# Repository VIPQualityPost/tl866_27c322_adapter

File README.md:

# tl866_27c322_adapter
A small footprint adapter that can be used for programming 27C* type EEPROMs on a TL866 II programmer. This programmer is abundantly available and cheap but does not support DIP packages larger than 2x20 pins. This adapter allows you to manually address the upper 3 bits of the memory so you can program these larger chips. Unlike some of the other cheaper adapters online, this one is very small, and uses a rotary bit switch to select the active bank with "true" code, so that you don't have to worry about switching the binary banks in the right order or with inverted output.

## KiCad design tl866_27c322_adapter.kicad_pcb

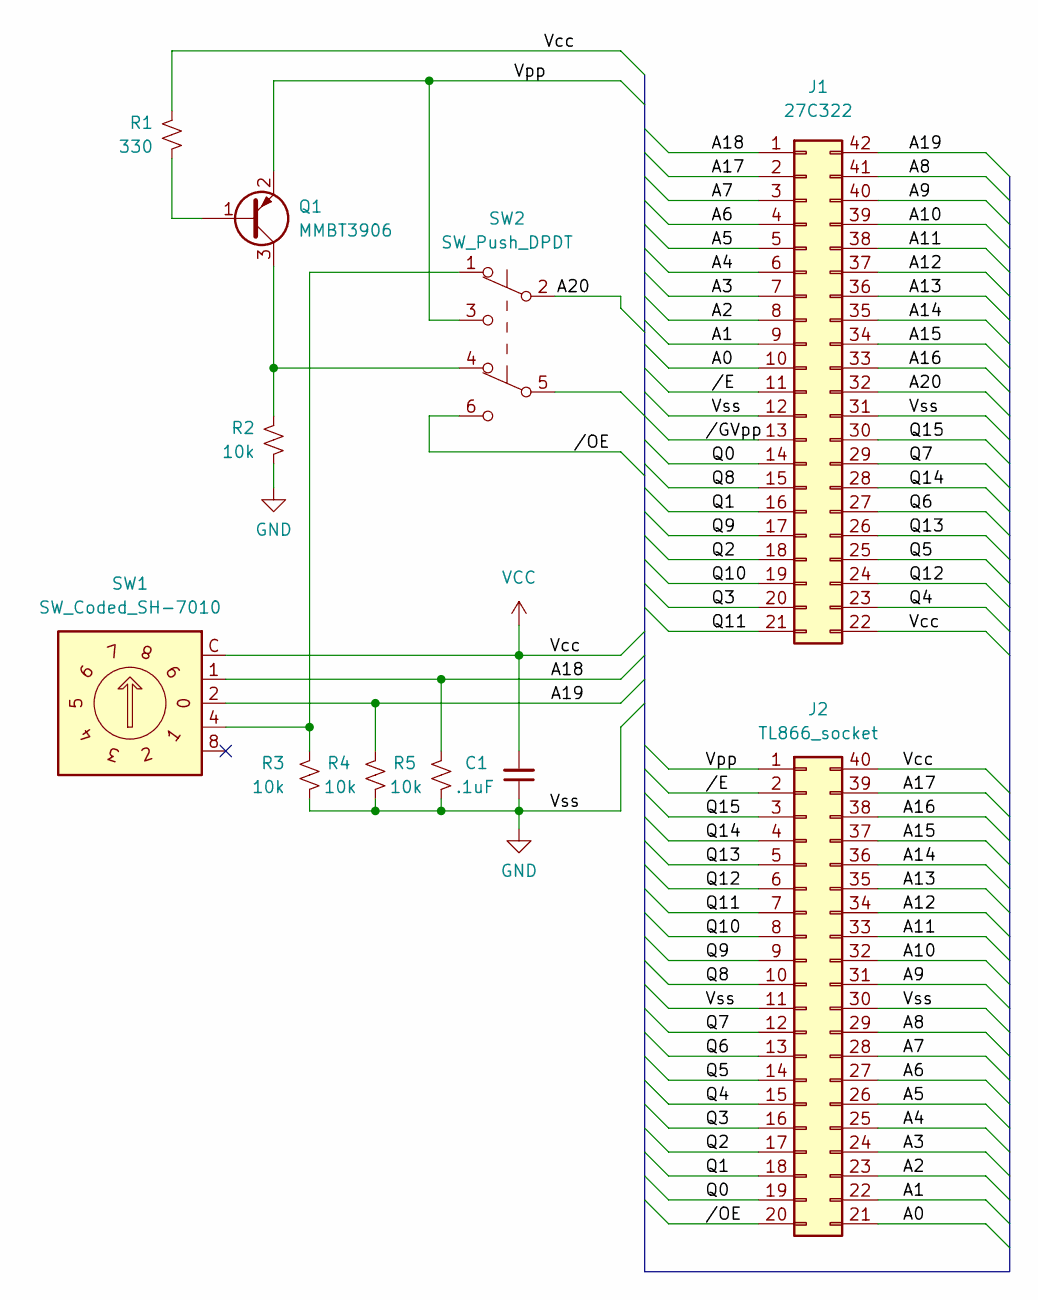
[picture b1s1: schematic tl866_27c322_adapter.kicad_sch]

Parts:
C1: .1uF; R_0805_2012Metric
J1: 27C322; DIP-42_W15.24mm
J2: TL866_socket; DIP-40_W15.24mm
Q1: MMBT3906; SOT-23
R1: 330; R_0805_2012Metric
R2, R3, R4, R5: 10k; R_0805_2012Metric
SW1: SW_Coded_SH-7010; Nidec_Copal_SH-7010B
SW2: SW_Push_DPDT; JS202011JCQN

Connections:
/A0: J1.10, J2.21
/A1: J1.9, J2.22
/A2: J1.8, J2.23
/A3: J1.7, J2.24
/A4: J1.6, J2.25
/A5: J1.5, J2.26
/A6: J1.4, J2.27
/A7: J1.3, J2.28
/A8: J1.41, J2.29
/A9: J1.40, J2.31
/A10: J1.39, J2.32
/A11: J1.38, J2.33
/A12: J1.37, J2.34
/A13: J1.36, J2.35
/A14: J1.35, J2.36
/A15: J1.34, J2.37
/A16: J1.33, J2.38
/A17: J1.2, J2.39
/A18: J1.1, R5.2, SW1.1
/A19: J1.42, R4.2, SW1.2
/A20: J1.32, SW2.2 (B)
/Q0: J1.14, J2.19
/Q1: J1.16, J2.18
/Q2: J1.18, J2.17
/Q3: J1.20, J2.16
/Q4: J1.23, J2.15
/Q5: J1.25, J2.14
/Q6: J1.27, J2.13
/Q7: J1.29, J2.12
/Q8: J1.15, J2.10
/Q9: J1.17, J2.9
/Q10: J1.19, J2.8
/Q11: J1.21, J2.7
/Q12: J1.24, J2.6
/Q13: J1.26, J2.5
/Q14: J1.28, J2.4
/Q15: J1.30, J2.3
/Vpp: J2.1, Q1.2 (E), SW2.3 (C)
//E: J1.11, J2.2
//GVpp: J1.13, SW2.5 (B)
//OE: J2.20, SW2.6 (C)
GND: C1.1, J1.12, J1.31, J2.11, J2.30, R2.1, R3.1, R4.1, R5.1
unnamed: Q1.1 (B), R1.1
unnamed: Q1.3 (C), R2.2, SW2.4 (A)
unnamed: R3.2, SW1.4, SW2.1 (A)
VCC: C1.2, J1.22, J2.40, R1.2, SW1.C

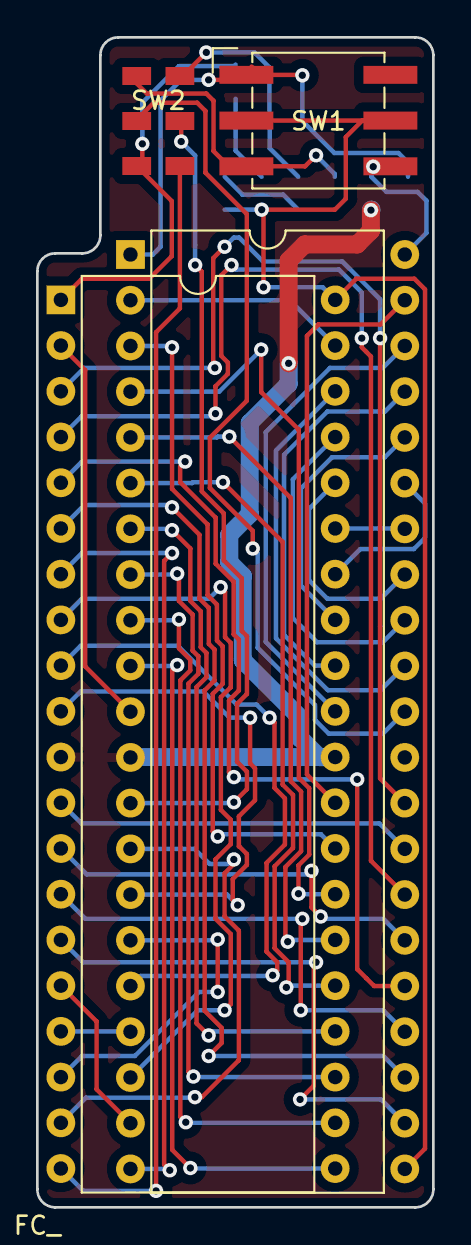
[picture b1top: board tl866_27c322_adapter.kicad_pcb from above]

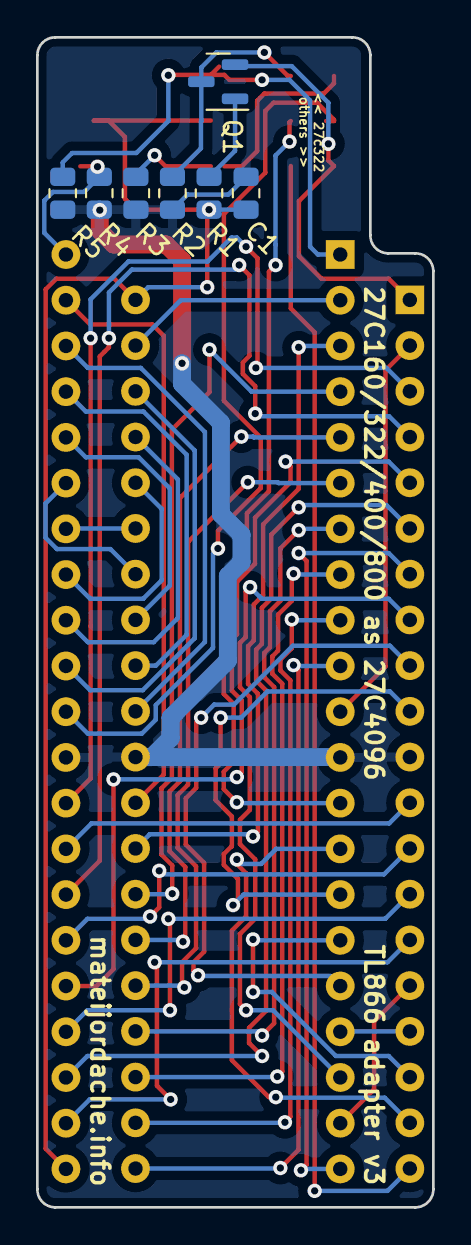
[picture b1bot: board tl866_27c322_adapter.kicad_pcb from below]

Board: 2 copper layers, 22.0 x 65.0 mm, 12 parts (7 on the bottom side), 46 nets.

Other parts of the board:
FC_: Val_; tl866_27c322adapter

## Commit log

2022-11-18 added files
2023-02-13 Auto-commit Mon Feb 13 12:20:03 EST 2023
2023-02-17 Auto-commit Thu Feb 16 21:34:56 EST 2023
2023-02-17 Auto-commit Fri Feb 17 12:27:44 EST 2023
2023-02-17 Auto-commit Fri Feb 17 13:04:02 EST 2023
2023-02-17 Remove ignored files
2023-02-18 Auto-commit Fri Feb 17 21:15:45 EST 2023
2023-02-18 update image name
2023-04-30 Auto-commit Sun Apr 30 10:54:39 EDT 2023
2023-05-14 Auto-commit Sun May 14 18:30:02 EDT 2023
